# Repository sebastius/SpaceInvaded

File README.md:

# SpaceInvaded
Clone of the original arcade

Based on Grant Searle's work: http://searle.x10host.com/spaceInvaders/index.html

Old blogs i did years ago: 

https://knutselblog.tweakblogs.net/blog/10321/buildlog-space-invaders-ram-adressering-en-isolatie.html
https://knutselblog.tweakblogs.net/blog/10273/buildlog-space-invaders-timing-and-video.html

https://knutselblog.tweakblogs.net/blog/10442/de-invasie-is-begonnen%21.html

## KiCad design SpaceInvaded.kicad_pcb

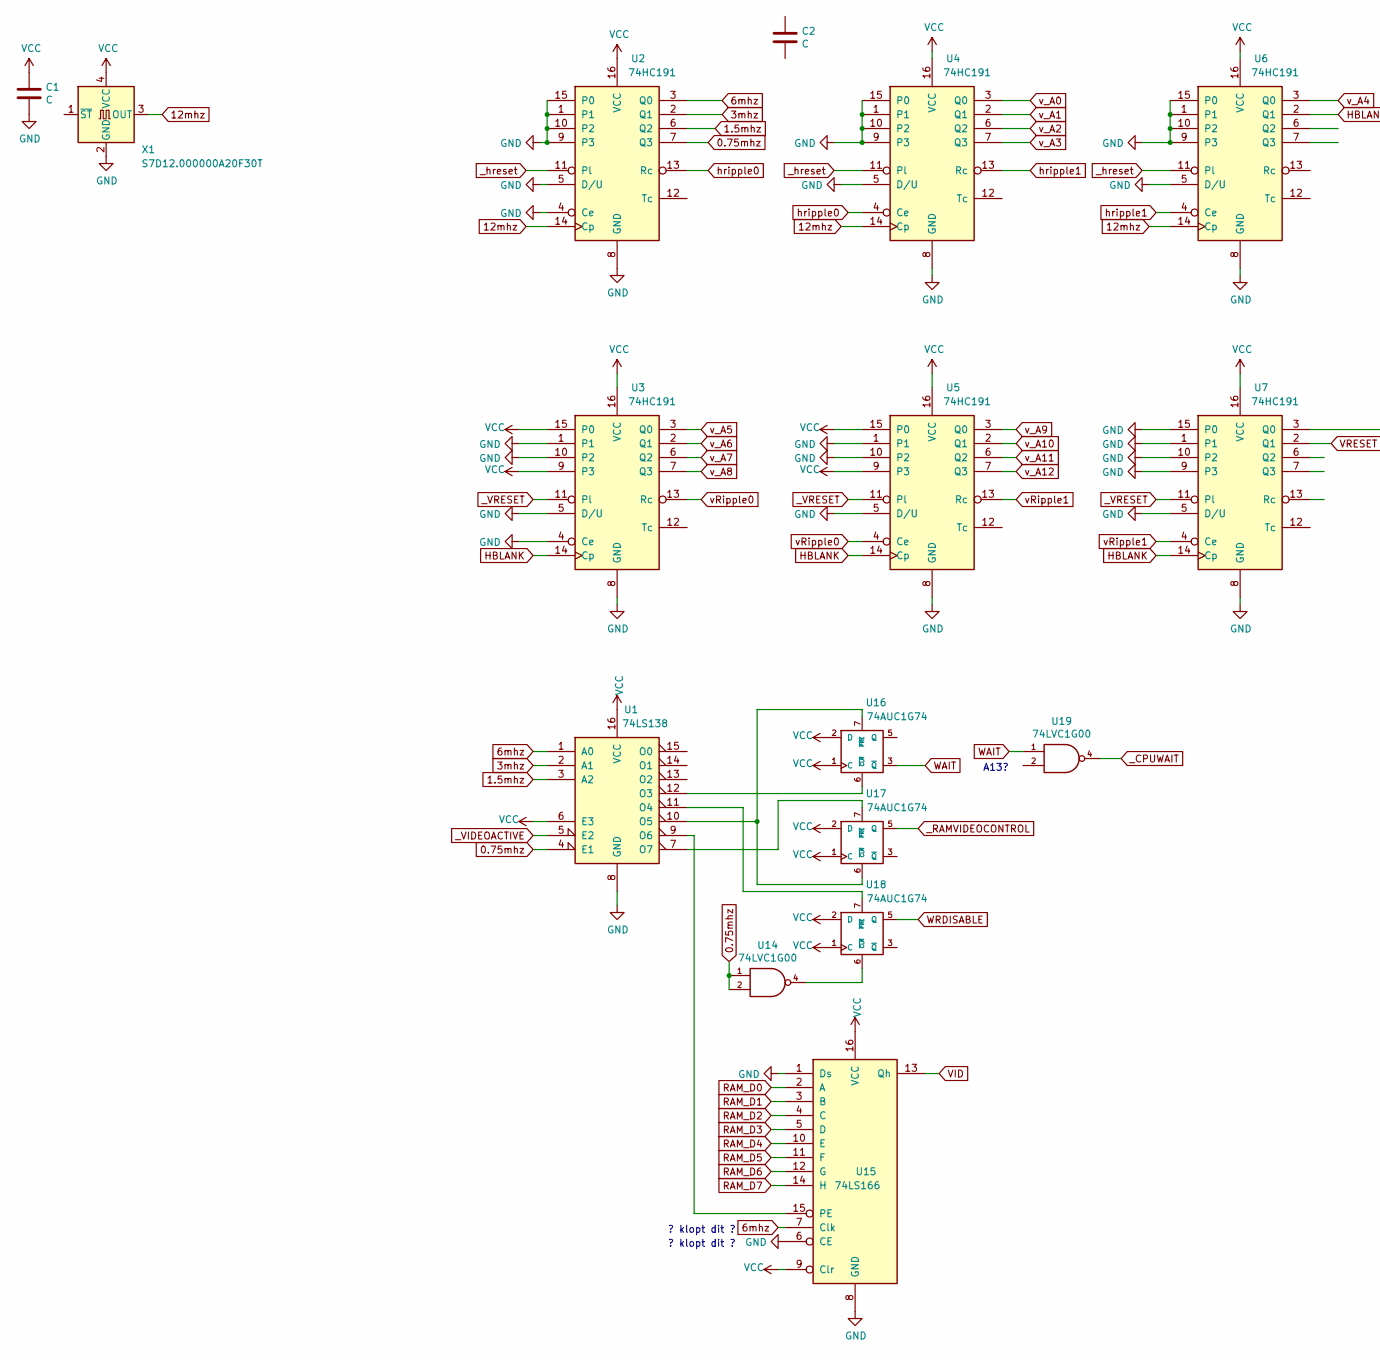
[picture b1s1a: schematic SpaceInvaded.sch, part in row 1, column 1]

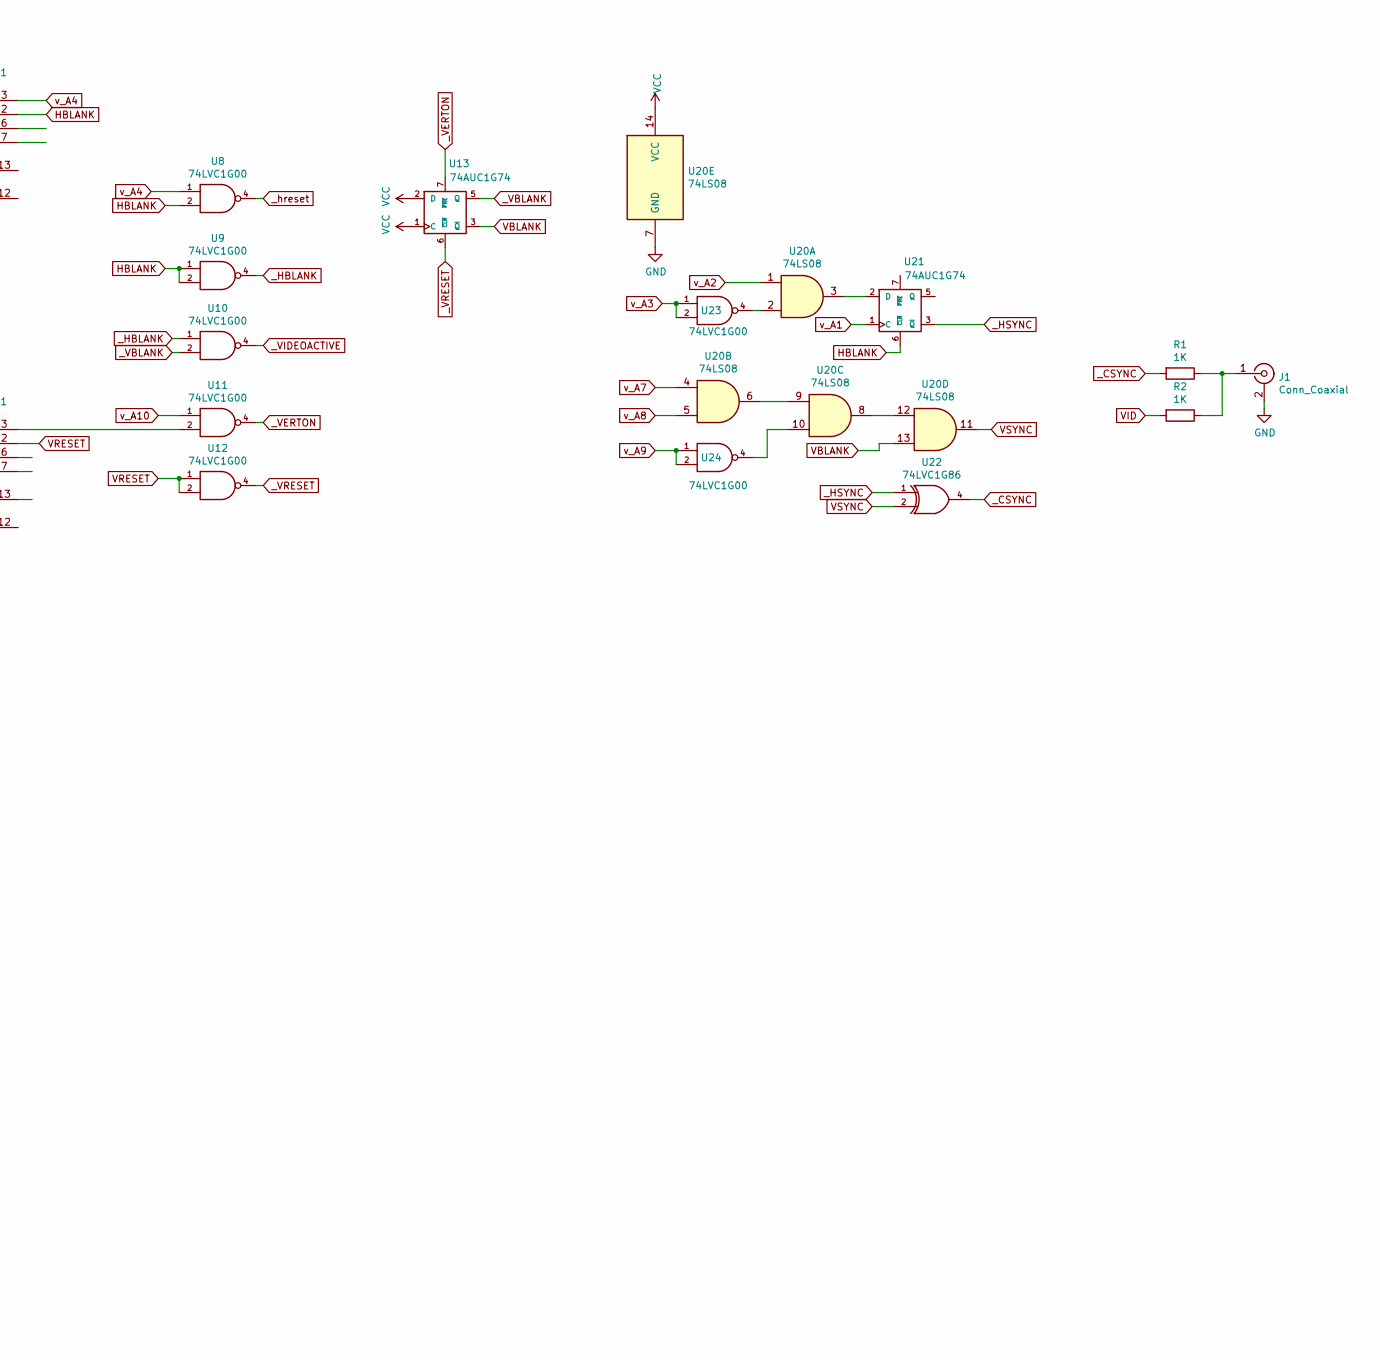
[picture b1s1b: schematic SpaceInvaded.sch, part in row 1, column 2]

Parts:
C1, C2: C; C_0603_1608Metric; LCSC C14663
J1: Conn_Coaxial
R1, R2: 1K; R_0603_1608Metric; LCSC C21190
U1: 74LS138; SOIC-16_3.9x9.9mm_P1.27mm; LCSC C5602
U2, U3, U4, U5, U6, U7: 74HC191; SOIC-16_3.9x9.9mm_P1.27mm; LCSC C5615
U8, U9, U10, U11, U12, U14, U19, U23, U24: 74LVC1G00; SOT-353_SC-70-5; LCSC C8185
U13, U16, U17, U18, U21: 74AUC1G74; VSSOP-8_2.3x2mm_P0.5mm; LCSC C503431
U15: 74LS166; SOIC-16_3.9x9.9mm_P1.27mm; LCSC C131891
U20: 74LS08; SOIC-14_3.9x8.7mm_P1.27mm; LCSC C5593
U22: 74LVC1G86; SOT-353_SC-70-5; LCSC C12513
X1: S7D12.000000A20F30T; Oscillator_SMD_SeikoEpson_SG8002CA-4Pin_7.0x5.0mm; LCSC C386965

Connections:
0.75mhz: U1.4 (E1), U2.7 (Q3), U14.1, U14.2
1.5mhz: U1.3 (A2), U2.6 (Q2)
3mhz: U1.2 (A1), U2.2 (Q1)
6mhz: U1.1 (A0), U2.3 (Q0), U15.7 (Clk)
12mhz: U2.14 (Cp), U4.14 (Cp), U6.14 (Cp), X1.3 (OUT)
GND: C1.2, J1.2 (Ext), U1.8 (GND), U2.1, U2.4 (Ce), U2.5 (D/U), U2.8 (GND), U2.9 (P3), U2.10 (P2), U2.15 (P0), U3.1, U3.4 (Ce), U3.5 (D/U), U3.8 (GND), U3.10 (P2), U4.1, U4.5 (D/U), U4.8 (GND), U4.9 (P3), U4.10 (P2), U4.15 (P0), U5.1, U5.5 (D/U), U5.8 (GND), U5.10 (P2), U6.1, U6.5 (D/U), U6.8 (GND), U6.9 (P3), U6.10 (P2), U6.15 (P0), U7.1, U7.5 (D/U), U7.8 (GND), U7.9 (P3), U7.10 (P2), U7.15 (P0), U8.3 (GND), U9.3 (GND), U10.3 (GND), U11.3 (GND), U12.3 (GND), U13.4 (GND), U14.3 (GND), U15.1 (Ds), U15.6 (CE), U15.8 (GND), U16.4 (GND), U17.4 (GND), U18.4 (GND), U19.3 (GND), U20.7 (GND), U21.4 (GND), U22.3 (GND), U23.3 (GND), U24.3 (GND), X1.2 (GND)
HBLANK: U3.14 (Cp), U5.14 (Cp), U6.2 (Q1), U7.14 (Cp), U8.2, U9.1, U9.2, U21.6 (~CLR)
unnamed: J1.1 (In), R1.1, R2.1
unnamed: U1.7 (O7), U17.7 (~PRE)
unnamed: U1.9 (O6), U15.15 (PE)
unnamed: U1.10 (O5), U16.7 (~PRE), U17.6 (~CLR)
unnamed: U1.11 (O4), U18.7 (~PRE)
unnamed: U1.12 (O3), U16.6 (~CLR)
unnamed: U7.3 (Q0), U11.2
unnamed: U14.4, U18.6 (~CLR)
unnamed: U20.2, U23.4
unnamed: U20.3, U21.2 (D)
unnamed: U20.6, U20.9
unnamed: U20.10, U24.4
unnamed: U20.8, U20.12
RAM_D0: U15.2 (A)
RAM_D1: U15.3 (B)
RAM_D2: U15.4 (C)
RAM_D3: U15.5 (D)
RAM_D4: U15.10 (E)
RAM_D5: U15.11 (F)
RAM_D6: U15.12 (G)
RAM_D7: U15.14 (H)
VBLANK: U13.3 (~Q), U20.13
VCC: C1.1, U1.6 (E3), U1.16 (VCC), U2.16 (VCC), U3.9 (P3), U3.15 (P0), U3.16 (VCC), U4.16 (VCC), U5.9 (P3), U5.15 (P0), U5.16 (VCC), U6.16 (VCC), U7.16 (VCC), U8.5 (VCC), U9.5 (VCC), U10.5 (VCC), U11.5 (VCC), U12.5 (VCC), U13.1 (C), U13.2 (D), U13.8 (VCC), U14.5 (VCC), U15.9 (Clr), U15.16 (VCC), U16.1 (C), U16.2 (D), U16.8 (VCC), U17.1 (C), U17.2 (D), U17.8 (VCC), U18.1 (C), U18.2 (D), U18.8 (VCC), U19.5 (VCC), U20.14 (VCC), U21.8 (VCC), U22.5 (VCC), U23.5 (VCC), U24.5 (VCC), X1.4 (VCC)
VID: R2.2, U15.13 (Qh)
VRESET: U7.2 (Q1), U12.1, U12.2
VSYNC: U20.11, U22.2
WAIT: U16.3 (~Q), U19.1
WRDISABLE: U18.5 (Q)
_CPUWAIT: U19.4
_CSYNC: R1.2, U22.4
_HBLANK: U9.4, U10.1
_HSYNC: U21.3 (~Q), U22.1
_RAMVIDEOCONTROL: U17.5 (Q)
_VBLANK: U10.2, U13.5 (Q)
_VERTON: U11.4, U13.7 (~PRE)
_VIDEOACTIVE: U1.5 (E2), U10.4
_VRESET: U3.11 (Pl), U5.11 (Pl), U7.11 (Pl), U12.4, U13.6 (~CLR)
_hreset: U2.11 (Pl), U4.11 (Pl), U6.11 (Pl), U8.4
hripple0: U2.13 (Rc), U4.4 (Ce)
hripple1: U4.13 (Rc), U6.4 (Ce)
vRipple0: U3.13 (Rc), U5.4 (Ce)
vRipple1: U5.13 (Rc), U7.4 (Ce)
v_A0: U4.3 (Q0)
v_A1: U4.2 (Q1), U21.1 (C)
v_A2: U4.6 (Q2), U20.1
v_A3: U4.7 (Q3), U23.1, U23.2
v_A4: U6.3 (Q0), U8.1
v_A5: U3.3 (Q0)
v_A6: U3.2 (Q1)
v_A7: U3.6 (Q2), U20.4
v_A8: U3.7 (Q3), U20.5
v_A9: U5.3 (Q0), U24.1, U24.2
v_A10: U5.2 (Q1), U11.1
v_A11: U5.6 (Q2)
v_A12: U5.7 (Q3)

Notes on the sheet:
? klopt dit ?
A13?

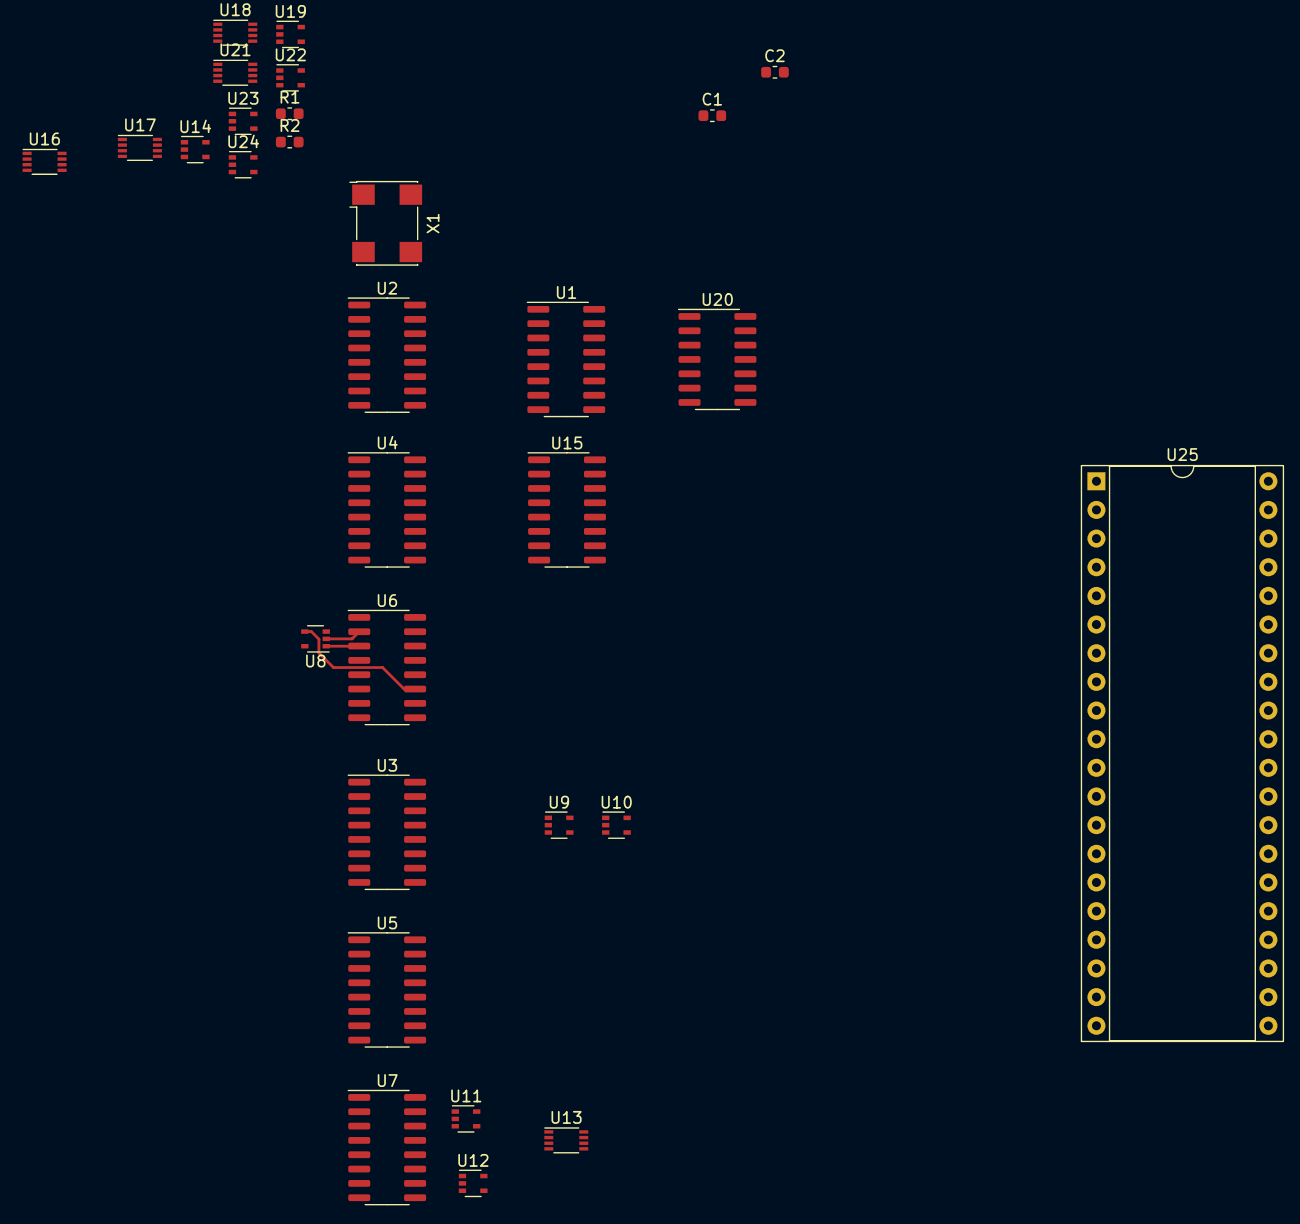
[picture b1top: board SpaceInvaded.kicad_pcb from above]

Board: 2 copper layers, 30 parts (0 on the bottom side), 46 nets.

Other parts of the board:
U25: Z80CPU; DIP-40_W15.24mm_Socket

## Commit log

2021-02-13 first commit
    things
